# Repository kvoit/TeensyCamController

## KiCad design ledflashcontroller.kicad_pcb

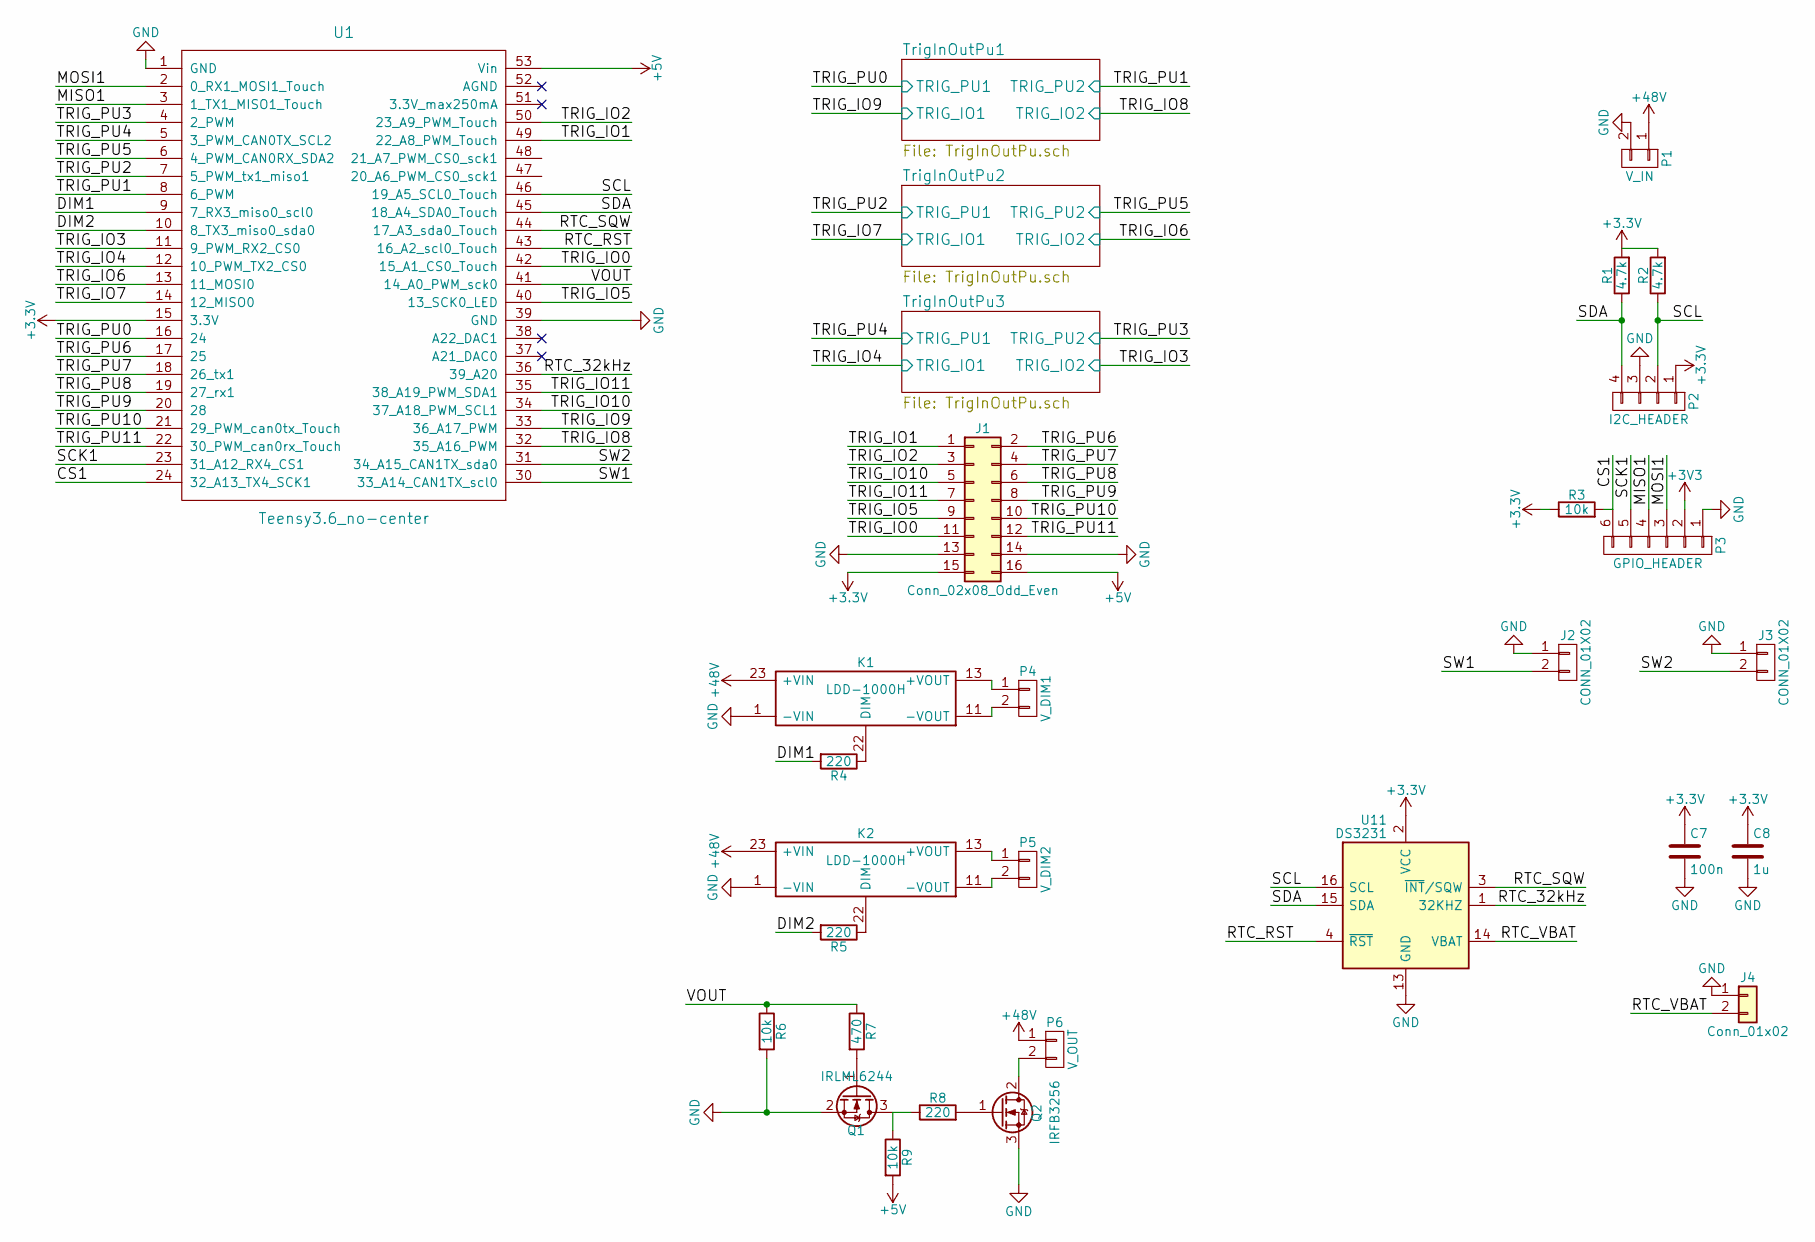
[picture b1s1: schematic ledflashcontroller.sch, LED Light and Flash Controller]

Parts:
C7: 100n; C_0603
C8: 1u; C_0603
J1: Conn_02x08_Odd_Even; Pin_Header_Straight_2x08_Pitch2.54mm_SMD
J2, J3: CONN_01X02; Pin_Header_Straight_1x02_Pitch2.54mm
J4: Conn_01x02; Pin_Header_Straight_1x02_Pitch2.54mm
K1, K2: LDD-1000H
P1: V_IN; DELTRON_571_x2
P2: I2C_HEADER; Pin_Header_Straight_1x04_Pitch2.54mm
P3: GPIO_HEADER; Pin_Header_Straight_1x06_Pitch2.54mm
P4: V_DIM1; DELTRON_571_x2
P5: V_DIM2; DELTRON_571_x2
P6: V_OUT; DELTRON_571_x2
Q1: IRLML6244; SOT-23_Handsoldering
Q2: IRFB3256; TO-220_Vertical
R1, R2: 4.7k; R_1206_HandSoldering
R3, R6, R9: 10k; R_1206_HandSoldering
R4, R5, R8: 220; R_1206_HandSoldering
R7: 470; R_1206_HandSoldering
U1: Teensy3.6_no-center; Teensy35_36_no-center
U11: DS3231; SOIC-16W_7.5x10.3mm_Pitch1.27mm

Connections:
+5V: J1.16, R9.2, U1.53 (Vin); also elsewhere on the board
+48V: K1.23 (+VIN), K2.23 (+VIN), P1.1, P6.1
/CS1: P3.6, R3.2, U1.24 (32_A13_TX4_SCK1)
/DIM1: R4.2, U1.9 (7_RX3_miso0_scl0)
/DIM2: R5.2, U1.10 (8_TX3_miso0_sda0)
/MISO1: P3.4, U1.3 (1_TX1_MISO1_Touch)
/MOSI1: P3.3, U1.2 (0_RX1_MOSI1_Touch)
/RTC_32kHz: U1.36 (39_A20), U11.1 (32KHZ)
/RTC_RST: U1.43 (16_A2_scl0_Touch), U11.4 (~RST)
/RTC_SQW: U1.44 (17_A3_sda0_Touch), U11.3 (~INT~/SQW)
/RTC_VBAT: J4.2, U11.14 (VBAT)
/SCK1: P3.5, U1.23 (31_A12_RX4_CS1)
/SCL: P2.2, R2.1, U1.46 (19_A5_SCL0_Touch), U11.16 (SCL)
/SDA: P2.4, R1.1, U1.45 (18_A4_SDA0_Touch), U11.15 (SDA)
/SW1: J2.2, U1.30 (33_A14_CAN1TX_scl0)
/SW2: J3.2, U1.31 (34_A15_CAN1TX_sda0)
/TRIG_IO0: J1.11, U1.42 (15_A1_CS0_Touch)
/TRIG_IO1: J1.1, U1.49 (22_A8_PWM_Touch)
/TRIG_IO2: J1.3, U1.50 (23_A9_PWM_Touch)
/TRIG_IO3: U1.11 (9_PWM_RX2_CS0); also elsewhere on the board
/TRIG_IO4: U1.12 (10_PWM_TX2_CS0); also elsewhere on the board
/TRIG_IO5: J1.9, U1.40 (13_SCK0_LED)
/TRIG_IO6: U1.13 (11_MOSI0); also elsewhere on the board
/TRIG_IO7: U1.14 (12_MISO0); also elsewhere on the board
/TRIG_IO8: U1.32 (35_A16_PWM); also elsewhere on the board
/TRIG_IO9: U1.33 (36_A17_PWM); also elsewhere on the board
/TRIG_IO10: J1.5, U1.34 (37_A18_PWM_SCL1)
/TRIG_IO11: J1.7, U1.35 (38_A19_PWM_SDA1)
/TRIG_PU0: U1.16 (24); also elsewhere on the board
/TRIG_PU1: U1.8 (6_PWM); also elsewhere on the board
/TRIG_PU2: U1.7 (5_PWM_tx1_miso1); also elsewhere on the board
/TRIG_PU3: U1.4 (2_PWM); also elsewhere on the board
/TRIG_PU4: U1.5 (3_PWM_CAN0TX_SCL2); also elsewhere on the board
/TRIG_PU5: U1.6 (4_PWM_CAN0RX_SDA2); also elsewhere on the board
/TRIG_PU6: J1.2, U1.17 (25)
/TRIG_PU7: J1.4, U1.18 (26_tx1)
/TRIG_PU8: J1.6, U1.19 (27_rx1)
/TRIG_PU9: J1.8, U1.20 (28)
/TRIG_PU10: J1.10, U1.21 (29_PWM_can0tx_Touch)
/TRIG_PU11: J1.12, U1.22 (30_PWM_can0rx_Touch)
/VOUT: R6.1, R7.1, U1.41 (14_A0_PWM_sck0)
GND: C7.2, C8.2, J1.13, J1.14, J2.1, J3.1, J4.1, K1.1 (-VIN), K2.1 (-VIN), P1.2, P2.3, P3.1, Q1.2 (S), Q2.3 (S), R6.2, U1.1 (GND), U1.39 (GND), U11.5 (NC), U11.6 (NC), U11.7 (NC), U11.8 (NC), U11.9 (NC), U11.10 (NC), U11.11 (NC), U11.12 (NC), U11.13 (GND); also elsewhere on the board
unnamed: K1.11 (-VOUT), P4.2
unnamed: K1.13 (+VOUT), P4.1
unnamed: K1.22 (DIM), R4.1
unnamed: K2.11 (-VOUT), P5.2
unnamed: K2.13 (+VOUT), P5.1
unnamed: K2.22 (DIM), R5.1
unnamed: P6.2, Q2.2 (D)
unnamed: Q1.1 (G), R7.2
unnamed: Q1.3 (D), R8.1, R9.1
unnamed: Q2.1 (G), R8.2

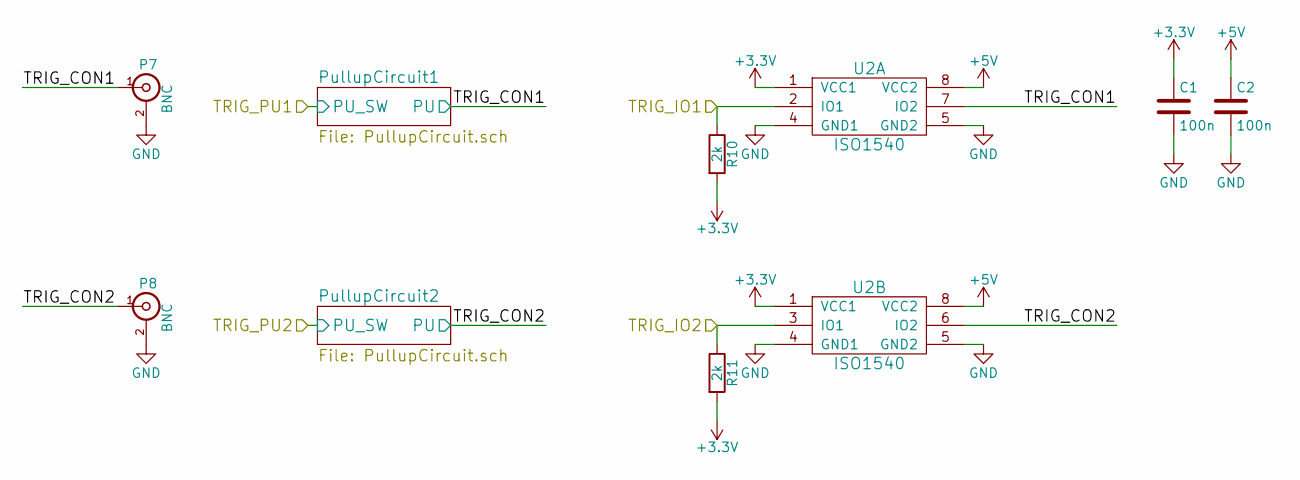
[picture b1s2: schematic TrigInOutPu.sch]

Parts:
C1, C2: 100n; C_0603_HandSoldering
P7, P8: BNC; BNC_Socket_RSpro_LargePads
R10, R11: 2k; R_0603_HandSoldering
U2: ISO1540; SOIC-8_3.9x4.9mm_Pitch1.27mm

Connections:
+5V: C2.1, U2.8 (VCC2); also elsewhere on the board
/TRIG_IO8: R11.1, U2.3 (IO1); also elsewhere on the board
/TRIG_IO9: R10.1, U2.2 (IO1); also elsewhere on the board
/TrigInOutPu1/TRIG_CON1: P7.1 (In), U2.7 (IO2); also elsewhere on the board
/TrigInOutPu1/TRIG_CON2: P8.1 (In), U2.6 (IO2); also elsewhere on the board
GND: C1.2, C2.2, P7.2 (Ext), P8.2 (Ext), U2.4 (GND1), U2.5 (GND2); also elsewhere on the board

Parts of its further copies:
C3, C4, C5, C6: 100n; C_0603_HandSoldering
P9, P10, P11, P12: BNC; BNC_Socket_RSpro_LargePads
R18, R19, R26, R27: 2k; R_0603_HandSoldering
U5, U8: ISO1540; SOIC-8_3.9x4.9mm_Pitch1.27mm

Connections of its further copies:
+5V: C4.1, C6.1, U5.8 (VCC2), U8.8 (VCC2); also elsewhere on the board
/TRIG_IO3: R27.1, U8.3 (IO1); also elsewhere on the board
/TRIG_IO4: R26.1, U8.2 (IO1); also elsewhere on the board
/TRIG_IO6: R19.1, U5.3 (IO1); also elsewhere on the board
/TRIG_IO7: R18.1, U5.2 (IO1); also elsewhere on the board
/TrigInOutPu2/TRIG_CON1: P9.1 (In), U5.7 (IO2); also elsewhere on the board
/TrigInOutPu2/TRIG_CON2: P10.1 (In), U5.6 (IO2); also elsewhere on the board
/TrigInOutPu3/TRIG_CON1: P11.1 (In), U8.7 (IO2); also elsewhere on the board
/TrigInOutPu3/TRIG_CON2: P12.1 (In), U8.6 (IO2); also elsewhere on the board
GND: C3.2, C4.2, C5.2, C6.2, P9.2 (Ext), P10.2 (Ext), P11.2 (Ext), P12.2 (Ext), U5.4 (GND1), U5.5 (GND2), U8.4 (GND1), U8.5 (GND2); also elsewhere on the board

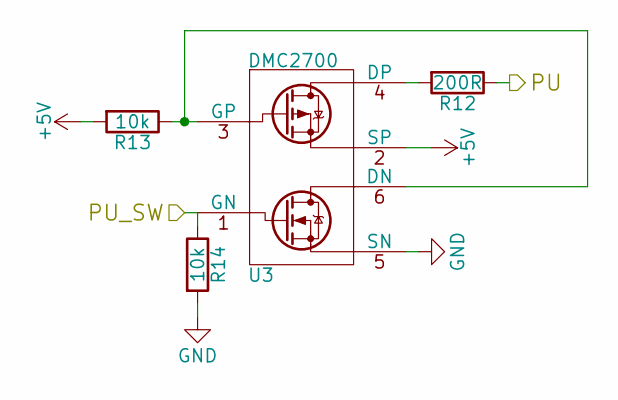
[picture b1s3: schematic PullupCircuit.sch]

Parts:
R12: 200R; R_1206_HandSoldering
R13, R14: 10k; R_0603_HandSoldering
U3: DMC2700; SOT-23-6_Handsoldering

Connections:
+5V: R13.2, U3.2 (SP); also elsewhere on the board
/TRIG_PU0: R14.1, U3.1 (GN); also elsewhere on the board
/TrigInOutPu1/TRIG_CON1: R12.1; also elsewhere on the board
GND: R14.2, U3.5 (SN); also elsewhere on the board
unnamed: R12.2, U3.4 (DP)
unnamed: R13.1, U3.3 (GP), U3.6 (DN)

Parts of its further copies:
R15, R20, R23, R28, R31: 200R; R_1206_HandSoldering
R16, R17, R21, R22, R24, R25, R29, R30, R32, R33: 10k; R_0603_HandSoldering
U4, U6, U7, U9, U10: DMC2700; SOT-23-6_Handsoldering

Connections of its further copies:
+5V: R16.2, R21.2, R24.2, R29.2, R32.2, U4.2 (SP), U6.2 (SP), U7.2 (SP), U9.2 (SP), U10.2 (SP); also elsewhere on the board
/TRIG_PU1: R17.1, U4.1 (GN); also elsewhere on the board
/TRIG_PU2: R22.1, U6.1 (GN); also elsewhere on the board
/TRIG_PU3: R33.1, U10.1 (GN); also elsewhere on the board
/TRIG_PU4: R30.1, U9.1 (GN); also elsewhere on the board
/TRIG_PU5: R25.1, U7.1 (GN); also elsewhere on the board
/TrigInOutPu1/TRIG_CON2: R15.1; also elsewhere on the board
/TrigInOutPu2/TRIG_CON1: R20.1; also elsewhere on the board
/TrigInOutPu2/TRIG_CON2: R23.1; also elsewhere on the board
/TrigInOutPu3/TRIG_CON1: R28.1; also elsewhere on the board
/TrigInOutPu3/TRIG_CON2: R31.1; also elsewhere on the board
GND: R17.2, R22.2, R25.2, R30.2, R33.2, U4.5 (SN), U6.5 (SN), U7.5 (SN), U9.5 (SN), U10.5 (SN); also elsewhere on the board
unnamed: R15.2, U4.4 (DP)
unnamed: R16.1, U4.3 (GP), U4.6 (DN)
unnamed: R20.2, U6.4 (DP)
unnamed: R21.1, U6.3 (GP), U6.6 (DN)
unnamed: R23.2, U7.4 (DP)
unnamed: R24.1, U7.3 (GP), U7.6 (DN)
unnamed: R28.2, U9.4 (DP)
unnamed: R29.1, U9.3 (GP), U9.6 (DN)
unnamed: R31.2, U10.4 (DP)
unnamed: R32.1, U10.3 (GP), U10.6 (DN)

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
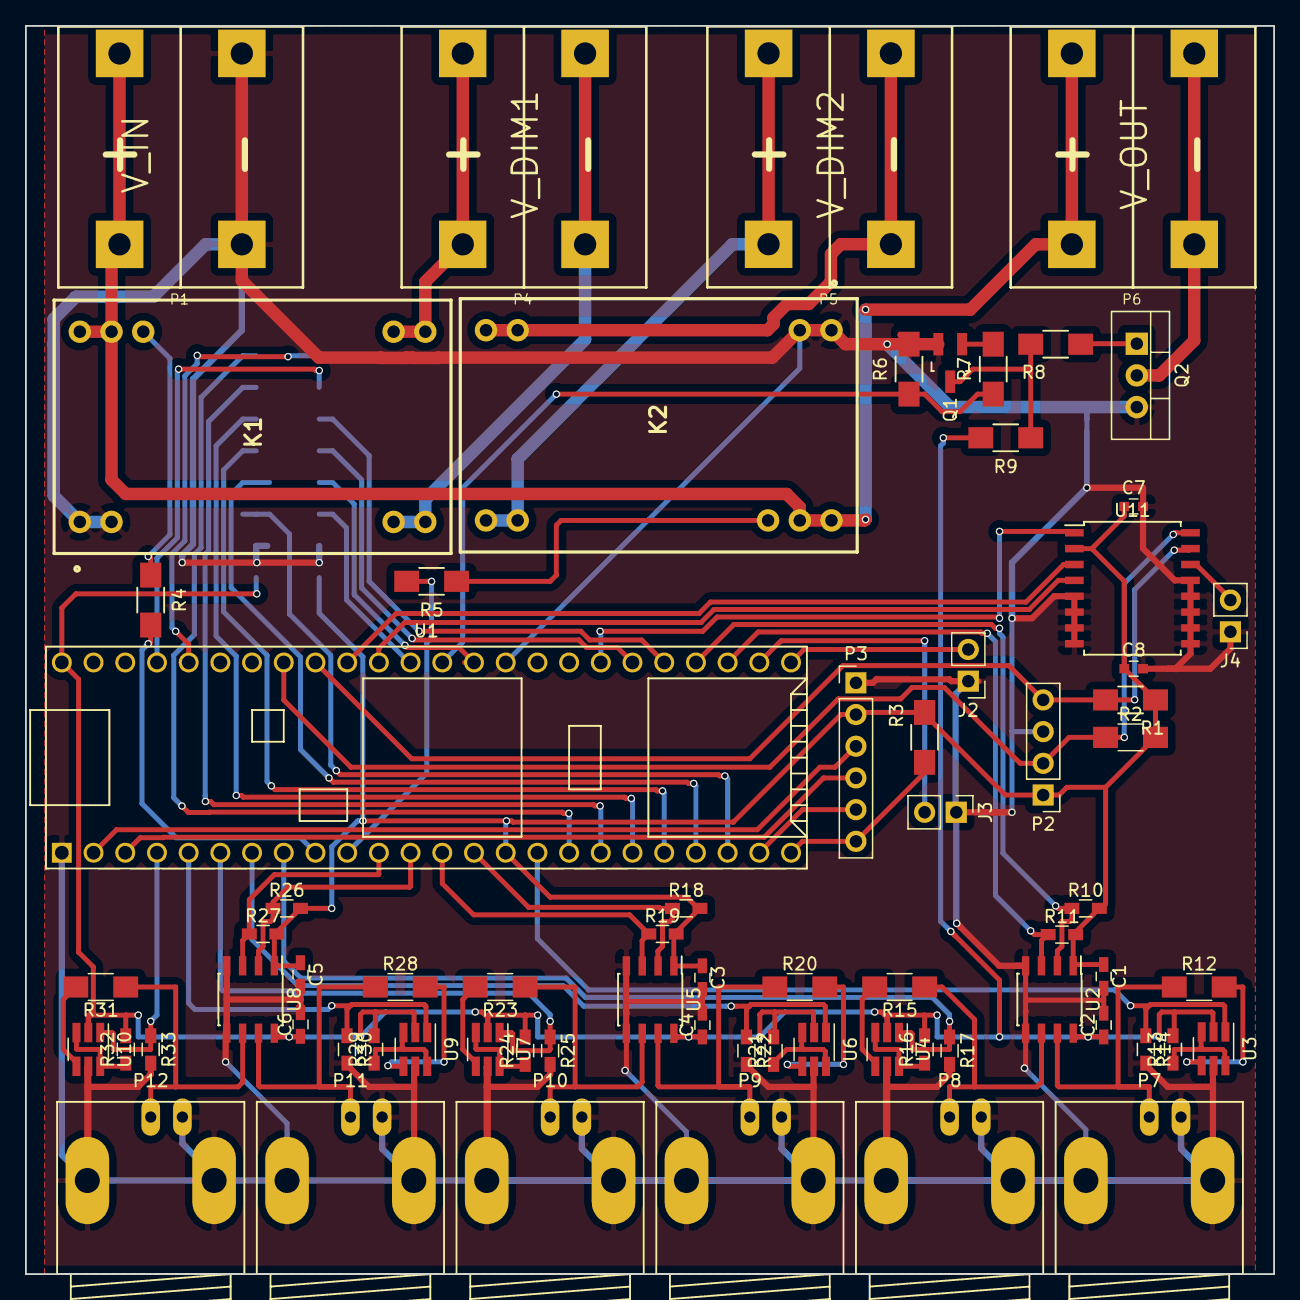
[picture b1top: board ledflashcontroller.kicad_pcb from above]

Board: 2 copper layers, 100.0 x 100.0 mm, 72 parts (1 on the bottom side), 71 nets.

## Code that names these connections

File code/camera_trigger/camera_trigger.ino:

#include "TeensyDelay.h"    // https://github.com/luni64/TeensyDelay

IntervalTimer frameTimer;

// Onboard LED
const uint8_t PIN_LED = 13;

// Trigger IO curcuit (left to right)
const uint8_t PIN_TRIG_IO1 = 9;
//const uint8_t PIN_TRIG_IO2 = 10;
//const uint8_t PIN_TRIG_IO3 = 11;
//const uint8_t PIN_TRIG_IO4 = 12;
//const uint8_t PIN_TRIG_IO5 = 35;
//const uint8_t PIN_TRIG_IO6 = 36;

// Trigger PU curcuit (left to right)
const uint8_t PIN_TRIG_PU1 = 2;
//const uint8_t PIN_TRIG_PU2 = 3;
//const uint8_t PIN_TRIG_PU3 = 4;
//const uint8_t PIN_TRIG_PU4 = 5;
//const uint8_t PIN_TRIG_PU5 = 6;
//const uint8_t PIN_TRIG_PU6 = 0; // no pullup ?

// not necessary
volatile bool triggerRunning = false;

volatile float framerate = 150; // Hz
volatile float frame_period = 1000. / framerate; // ms
const float framerate_min = 0.5; // Hz

volatile float exposure_time = 2.5; // ms
const float exposure_time_min = 0.5; // ms
volatile bool timerExposure = true;

volatile long camOnMicros = 0.;
volatile long triggerStart = 0;


char* cmd;
float arg;


void camOnCallback()
{
  digitalWriteFast(PIN_TRIG_IO1, LOW);
  pinMode(PIN_TRIG_IO1, OUTPUT);
}

void camOffCallback()
{
  pinMode(PIN_TRIG_IO1, INPUT);
  digitalWriteFast(PIN_TRIG_IO1, LOW); // digitalWriteFast?
}

void setFrameRate(float framerate_a)
{
  framerate = max(floor(10. * framerate_a) / 10., framerate_min); // truncates to one significant digit
  frame_period = 1000. / framerate; // ms
}

void setExposureTime(float exposure_time_a)
{
  exposure_time = max(floor(10. * exposure_time_a) / 10., exposure_time_min); // truncates to one significant digit 
}

void triggerOnCallback()
{
  if (!triggerRunning)
  {
    triggerRunning = true;
    digitalWrite(PIN_LED, HIGH);
    //frameTimer.end();

    // TeensyDelay::Trigger() does not work accordingly for delays >= 32
    if (exposure_time < 32)
    {
      timerExposure = true;
    }
    else
    {
      timerExposure = false;
    }

    triggerStart = micros();
    frameTimer.begin(triggerOn, 1000. * frame_period);
  }
}

void triggerOn()
{
  camOnCallback();
  camOnMicros = micros();
  Serial.println(camOnMicros - triggerStart);
  if (timerExposure)
  {
    TeensyDelay::trigger(1000. * exposure_time, 0); // cam off
  }
}

void triggerOffCallback()
{
  if (triggerRunning)
  {
    triggerRunning = false;
    digitalWrite(PIN_LED, LOW);
    frameTimer.end();
    camOffCallback();
  } 
}

void read_cmd_and_arg(char* &cmd, float &arg)
{
  char cmd_all [256];
  char* arg_str;

  sprintf(cmd_all, Serial.readString().c_str());
  
  cmd = strtok(cmd_all, " ");
//  a = int(atof(cmd_str_separated));
  arg_str = strtok(NULL, " ");
  arg = atof(arg_str);
}


void setup() {
  // Set up onboard LED (off)
  pinMode(PIN_LED, OUTPUT);  
  digitalWrite(PIN_LED, LOW); 

  // Set up pullup (on)
  pinMode(PIN_TRIG_PU1, OUTPUT);
  digitalWrite(PIN_TRIG_PU1, HIGH);

  TeensyDelay::begin();
  TeensyDelay::addDelayChannel(camOffCallback); //setup channel 0

  // Initialize variables
//  sprintf(cmd, "NO_CMD");
//  arg = -1.0;

  // Set up serial
  Serial.begin(115200);
  delay(1000); // wait for serial 
}

void loop() {
  // turns cameras off in case exposure time >= 32
  if(!timerExposure & ((micros() - 1000. * exposure_time) >= camOnMicros))
  {
    timerExposure = true;
    camOffCallback();
  }
  
  if (Serial.available() > 0)
  {
    read_cmd_and_arg(cmd, arg);
//    Serial.print("cmd: ");
//    Serial.println(cmd);
//    Serial.print("arg: ");
//    Serial.println(arg);

    if (strcmp(cmd, "TRIGGER_ON") == 0)
    {
      triggerOnCallback();
    }
    else if (strcmp(cmd, "TRIGGER_OFF") == 0)
    {
      triggerOffCallback();
    }
    else if (strcmp(cmd, "FRAMERATE") == 0)
    {
      setFrameRate(arg);
    }
    else if (strcmp(cmd, "EXPOSURE") == 0)
    {
      setExposureTime(arg);
    }
    sprintf(cmd, "NO_CMD");
    arg = 0.0;
    Serial.clear();
  }
}

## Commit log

2017-09-12 Initial commi
2017-10-20 Fixed some annotations and footprints
2017-10-23 Restructured existing connections and aligned everythink to grid
2017-10-23 Duplicated existing circuits
2017-10-23 Fixed bugs (wires to close to pads)
2017-10-23 Connected circuits to Teensy
2017-10-23 Changed double-usage of pins
2017-10-23 Arranged components so that they are close to their respective circuits
2017-10-23 Bugfixes for vias to close to wires
2017-10-23 Completed Ratsnest
2017-10-23 Refinement
2017-10-23 Refinement2
2017-10-23 Push to update all files
2017-10-23 Added RTC in schematic
2017-10-23 RTC update
2017-10-23 Connected RTC and git tried to get rid of vias
2017-10-23 Minor change in wireing
2017-10-24 Minor change in wiring again
2017-10-24 Added groundplane
2017-10-25 fixed decoupling cap for U8
2017-10-25 fixed decoupling cap for U11
2017-10-25 Cleanups
2017-10-25 Fixed ISO1540 decoupling issue
2017-10-25 Cleanup teensy schematic and remove old custom.lib
2017-10-25 Add 2nd teensy ground and rotate mosfet. Fixes #3
2017-10-25 Increase LDD pinhole and pad
2017-10-25 Correct and add new LDD footprint to pcb
2017-10-25 Switched RTC_SQW and RTC_32kHz for improved routing
2017-10-25 Pushed some traces closer together
2017-10-26 Plot and add final v2 gerber files
2018-01-15 Add CAD drawings for box of V1
2018-01-15 Modified CAD drawings for the fisher-box to match v2 of the trigger box (cut outs)
2018-01-18 Inital commit for Teensy code to send external trigger signal
2018-01-22 Modified python code for communicating with the Teensy. Enabled writing the trigger signal to a file
2018-01-23 Minor esthetical changes
2018-01-23 More updates after testint with the actual setup. This seems to work now. Although, I am not sure yet if I got rid of the case where the file is closed in threat t2 while thread t1 still wants to rid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
2018-01-24 Added code so the two threads communicate correctly with each other.
2018-01-24 Just added a tiny comment
2018-01-24 Added time delay after sending trigger off signal. Recording trigger signal since sending trigger on signal
2018-01-24 Added timeout signal to for the read thread. Everything seems to work correctly now
